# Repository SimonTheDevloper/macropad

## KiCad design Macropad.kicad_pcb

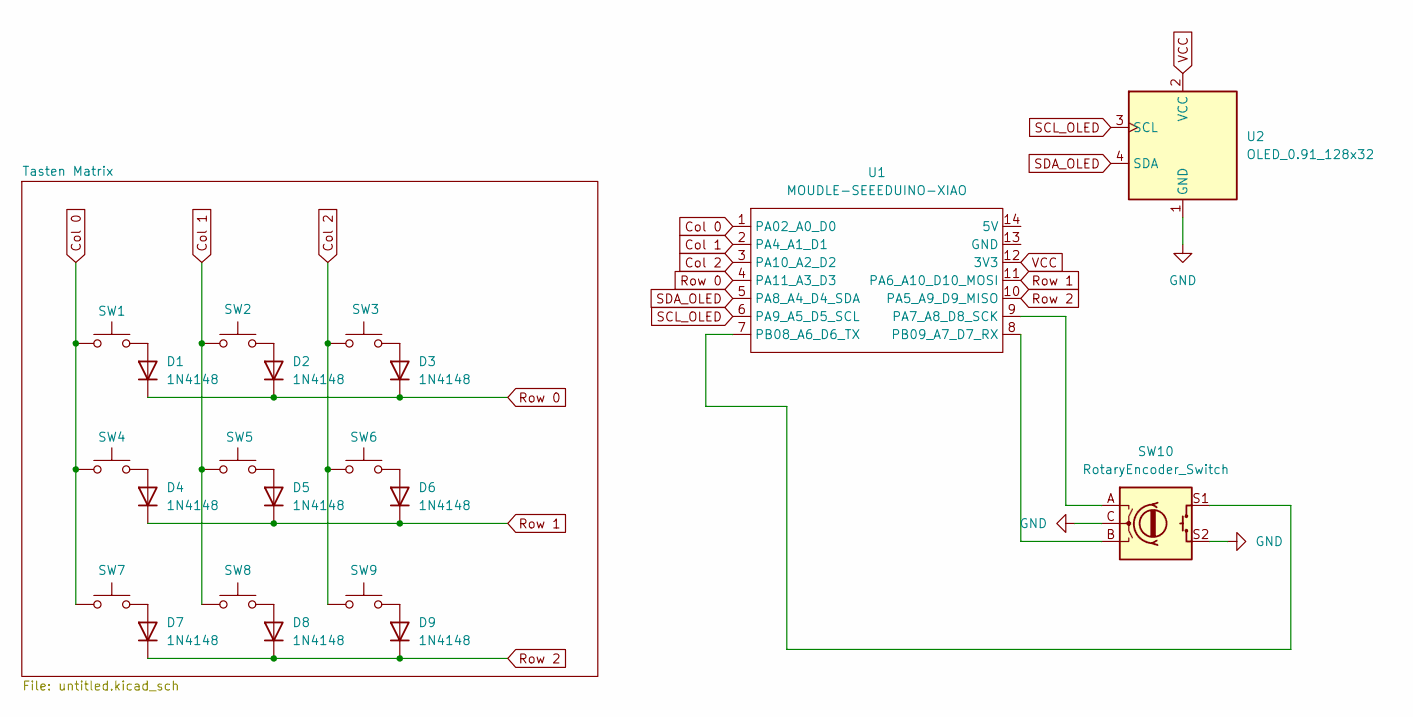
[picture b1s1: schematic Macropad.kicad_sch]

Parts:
D1, D2, D3, D4, D5, D6, D7, D8, D9: 1N4148; D_DO-35_SOD27_P7.62mm_Horizontal
SW1, SW2, SW3, SW4, SW5, SW6, SW7, SW8, SW9: SW_Push; SW_Cherry_MX_1.00u_PCB
SW10: RotaryEncoder_Switch; RotaryEncoder_Alps_EC11E-Switch_Vertical_H20mm_CircularMoun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
U1: MOUDLE-SEEEDUINO-XIAO; XIAO-Generic-Hybrid-14P-2.54-21X17.8MM
U2: OLED_0.91_128x32

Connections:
Col 0: SW1.1, SW4.1, SW7.1, U1.1 (PA02_A0_D0)
Col 1: SW2.1, SW5.1, SW8.1, U1.2 (PA4_A1_D1)
Col 2: SW3.1, SW6.1, SW9.1, U1.3 (PA10_A2_D2)
GND: SW10.C, SW10.S2, U2.1 (GND)
unnamed: D1.2 (A), SW1.2
unnamed: D2.2 (A), SW2.2
unnamed: D3.2 (A), SW3.2
unnamed: D4.2 (A), SW4.2
unnamed: D5.2 (A), SW5.2
unnamed: D6.2 (A), SW6.2
unnamed: D7.2 (A), SW7.2
unnamed: D8.2 (A), SW8.2
unnamed: D9.2 (A), SW9.2
unnamed: SW10.A, U1.9 (PA7_A8_D8_SCK)
unnamed: SW10.S1, U1.7 (PB08_A6_D6_TX)
unnamed: SW10.B, U1.8 (PB09_A7_D7_RX)
Row 0: D1.1 (K), D2.1 (K), D3.1 (K), U1.4 (PA11_A3_D3)
Row 1: D4.1 (K), D5.1 (K), D6.1 (K), U1.11 (PA6_A10_D10_MOSI)
Row 2: D7.1 (K), D8.1 (K), D9.1 (K), U1.10 (PA5_A9_D9_MISO)
SCL_OLED: U1.6 (PA9_A5_D5_SCL), U2.3 (SCL)
SDA_OLED: U1.5 (PA8_A4_D4_SDA), U2.4 (SDA)
VCC: U1.12 (3V3), U2.2 (VCC)

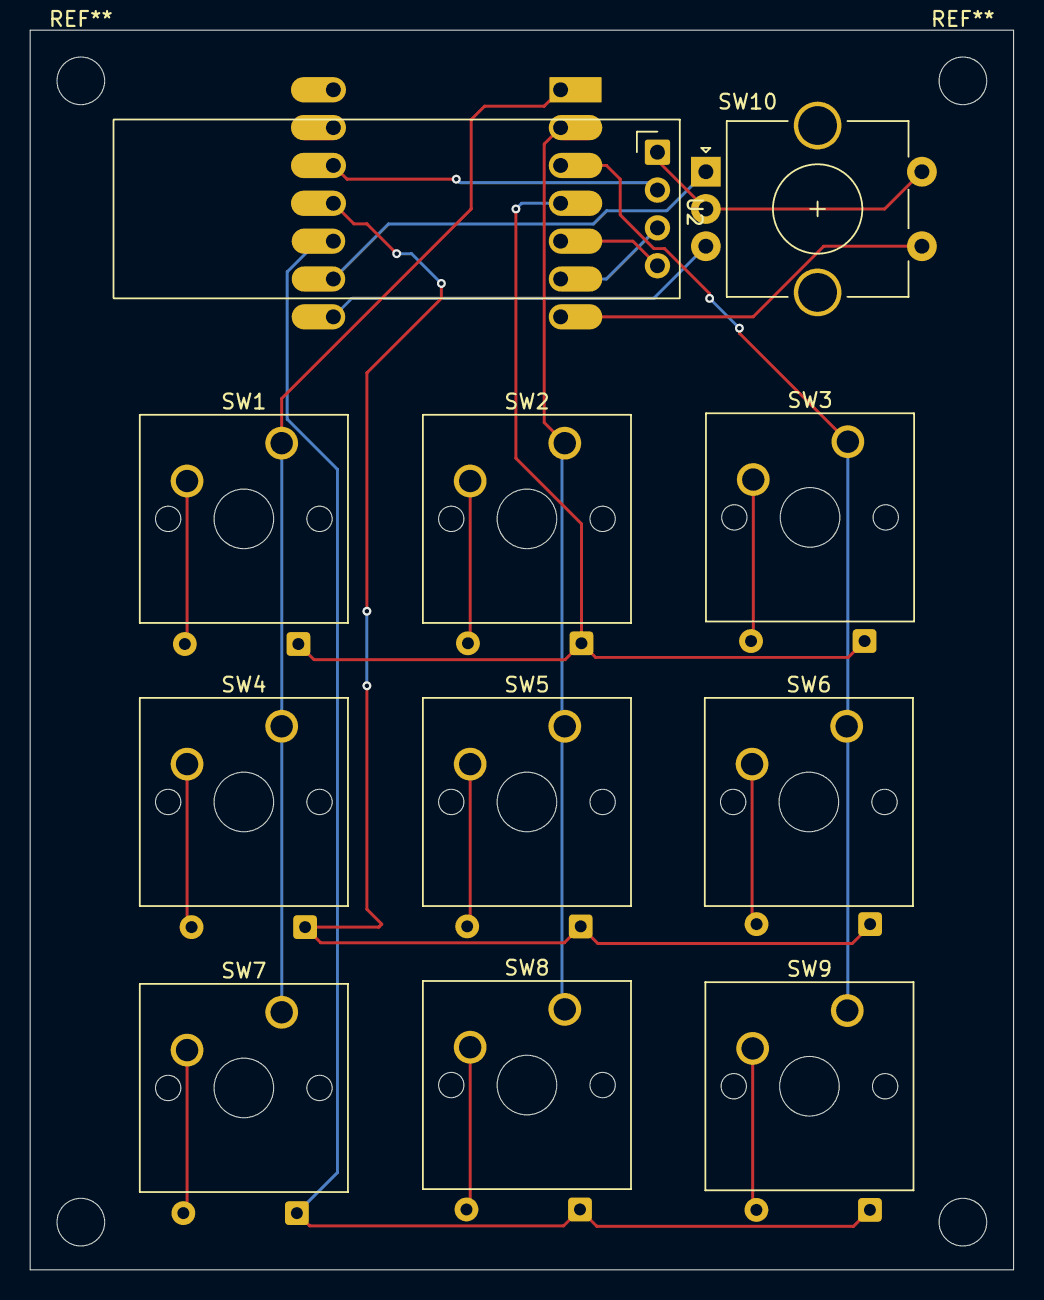
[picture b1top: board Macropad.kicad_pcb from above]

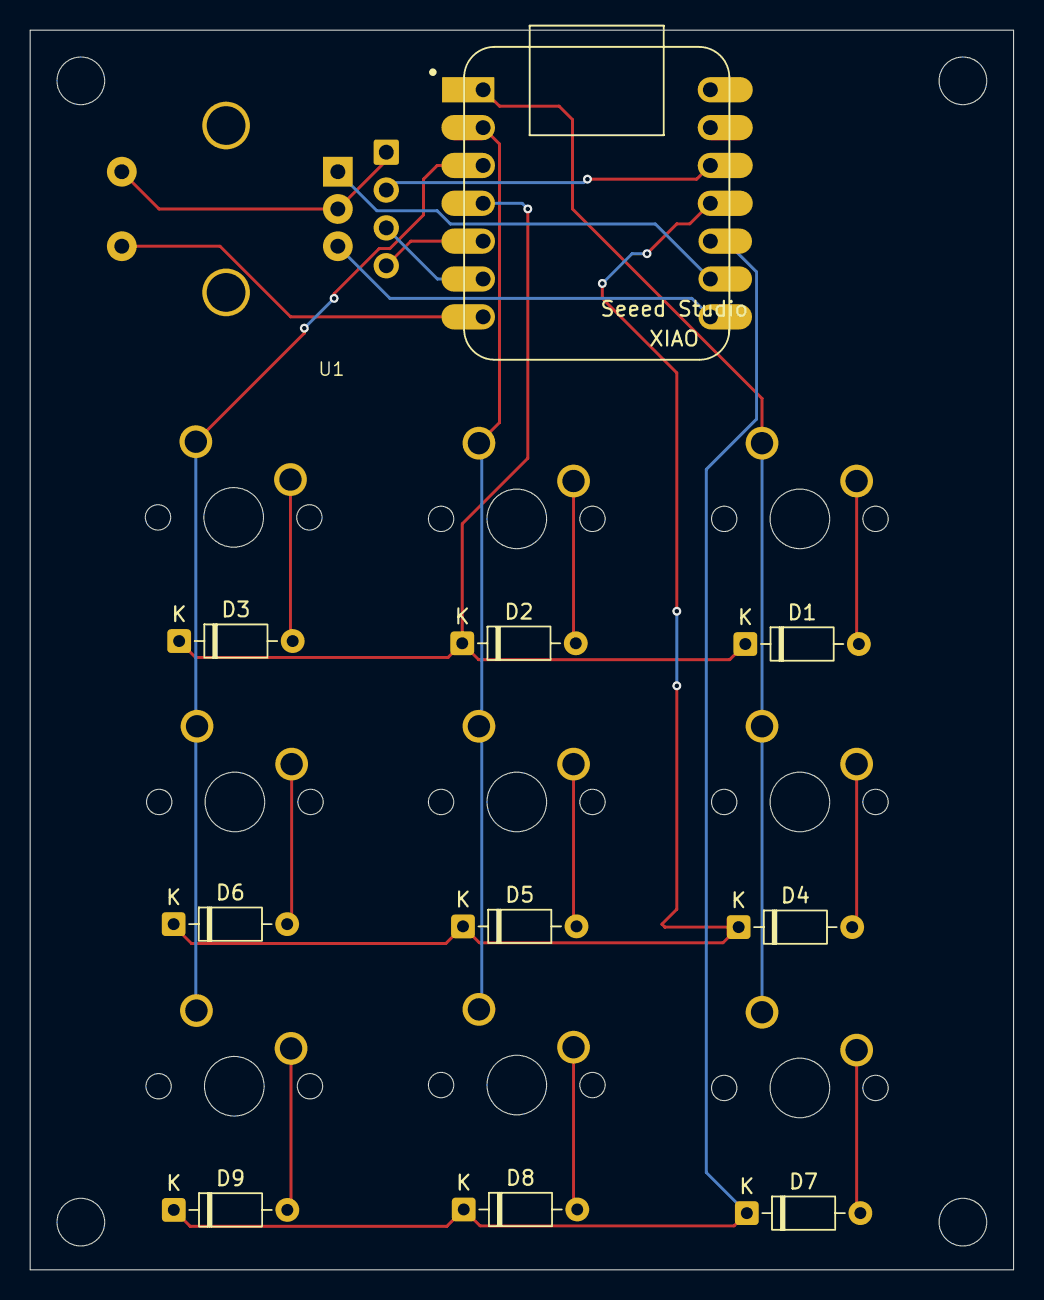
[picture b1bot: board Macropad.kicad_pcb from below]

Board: 2 copper layers, 66.0 x 83.2 mm, 21 parts (10 on the bottom side), 22 nets.

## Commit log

2026-03-16 Erster Commit: KiCad-Projekt initial
2026-03-16 Adjust schematic wires and add backup ZIP
    gitignore hinzugefügt die hoffentlich beachtet wird
2026-03-16 Create .gitignore
    feat: gitignore hinzugefügt
2026-03-16 Update Macropad.kicad_sch
    testveränderung
2026-03-22 feat: 3D Modlle noch hinzugefügt
2026-03-27 noch löcher hinzugefügt
